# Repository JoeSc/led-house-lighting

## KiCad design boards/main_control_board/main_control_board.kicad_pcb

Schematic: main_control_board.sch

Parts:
C1, C101, C104, C107, C112, C116, C123, C148, C1001, C1234, C1235: CAP_0P1UF_10P_50V_X7R_0805; Voltage 50V
C2, C102, C109, C110, C126, C127: CAP_1UF_10P_25V_X7R_0805; Voltage 25V
C103, C117, C118, C119, C120, C121, C122, C128, C129, C130, C131, C142, C145, C1002, C1008, C1011: CAP_2P2UF_10P_50V_X5R_1206; Voltage 50V
C111, C113, C114, C12345: CAP_22UF_20P_10V_X5R_1206; Voltage 10V
C124, C125: CAP_39PF_5P_50V_NP0_0805; Voltage 50V
C132, C133, C134, C135, C136, C137, C138, C139, C140, C141: CAP_1UF_10P_50V_X5R_0805; Voltage 50V
D1, D2, D101, D103, D107, D108, D109: DIODE_MBR0520_SOD123
D4: LED_BLUE_0805
D102, D104: LED_GREEN_DIFF_0805
D105, D106: LED_YELLOW_0805
D110, D111, D112, D113, D114: DIODE_MBRA340T3G_SMA
HW100, HW101, HW102, HW103: CONN_1
J101, J102: CONN_USB_MINI_B
L101, L102, L103, L104, L105: IND_39UH
P1: CONN_JST_PH_4
P2, P101: CONN_JST_PH_3
P102: CONN_JST_PH_2
P103: CONN_2
P104: CONN_5X2
P105, P106: CONN_TERM_BLOCK_2POS_3P5MM
P107: CONN_TERM_BLOCK_4POS_3P5MM
Q101: TR_N_SI2308BDS
Q102: MOSFET_P
R1, R2: RES_1K_1P_1V8W_0805
R5, R101, R105, R108, R109: RES_330_1P_1V8W_0805
R102, R106, R107, R110: RES_4P7K_1P_1V8W_0805
R103: RES_1P5K_1P_1V8W_0805
R104: RES_100K_1P_1V8W_0805
R111, R112, R113, R114, R115: RES_4P42K_1P_1V8W_0805
R116, R117, R118, R119, R120: RES_80P6K_1P_1V8W_0805
SW101, SW102: SW_PB_MJTP1230
U101, U102, U103, U104, U105: IC_LM3414_PSOP8
U1000: IC_LPC1343_LQFP48
U1010: IC_FT232RL_SSOP28
U1020: IC_XBEE_SMD
U1050: IC_MCP1700T33_SOT23
X101: CRYSTAL_12MHZ_18PF_CS3P2X5

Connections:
+3.3V: C1.1, C101.1, C107.1, C109.1, C110.1, C111.1, C112.1, C113.1, C114.1, C123.1, C127.1, C1234.1, C1235.1, P1.1, P2.1, P101.2, P104.3, Q102.S, R1.1, R2.1, R5.2, R102.1, R107.1, R108.2, R109.2, R110.1, U1000.8, U1000.44, U1010.4, U1020.1, U1050.2
+5V: C102.1, C104.1, C126.1, C12345.1, D103.2, J101.1, P102.2 (PM), U1010.20, U1050.3
+24V: C103.1, C116.1, C117.1, C118.1, C119.1, C120.1, C121.1, C122.1, C128.1, C129.1, C130.1, C131.1, C137.1, C138.1, C139.1, C140.1, C141.1, C142.1, C145.1, C148.1, C1002.1, C1008.1, C1011.1, D110.2, D111.2, D112.2, D113.2, D114.2, P103.2 (PM), P105.2 (PM), P106.2 (PM), P107.4, U101.8, U102.8, U103.8, U104.8, U105.8
/AD1: P104.10, U1000.32
/AD2: P104.9, U1000.33
/AD3: P104.8, U1000.34
/AD4: P104.7, U1000.35
/BLU_DIM: U103.6, U1000.29
/BLU_FS: R118.1, U103.5
/BLU_IADJ: R113.1, U103.3
/BLU_OUT: C139.2, L103.1, P107.1
/BLU_SW: D112.1, L103.2, U103.7
/BLU_VCC: C134.1, U103.1
/BOOTSEL_RESET: D108.2, D109.2, SW102.2
/BOOT_SEL: C123.2, D1.1, D2.1, D108.1, R110.2, U1000.4
/EXTRA_AD: P2.2, U1000.42
/GRN_DIM: U102.6, U1000.30
/GRN_FS: R117.1, U102.5
/GRN_IADJ: R112.1, U102.3
/GRN_OUT: C138.2, L102.1, P107.2 (PM)
/GRN_SW: D111.1, L102.2, U102.7
/GRN_VCC: C133.1, U102.1
/IIC_SCL: P1.2, R2.2, U1000.15
/IIC_SDA: P1.3, R1.2, U1000.16
/MOTION_DET: P101.3, U1000.24
/RED_DIM: U101.6, U1000.40
/RED_FS: R116.1, U101.5
/RED_IADJ: R111.1, U101.3
/RED_OUT: C137.2, L101.1, P107.3
/RED_SW: D110.1, L101.2, U101.7
/RED_VCC: C132.1, U101.1
/RELAY_EN: Q101.G, U1000.45
/SER_RX_LED: D106.2, U1010.22
/SER_RX_LED_R: D106.1, R109.1
/SER_TX_LED: D105.2, U1010.23
/SER_TX_LED_R: D105.1, R108.1
/SER_UCTOUSB: U1000.47, U1010.5, U1020.3
/SER_USBTOUC: U1000.46, U1010.1, U1020.2
/SER_USB_D: J101.3, U1010.15
/SW1: P104.4, U1000.38
/SW2: P104.6, U1000.36
/SW3: P104.5, U1000.37
/SW4: P104.2, U1000.39
/UC_D: J102.3, R103.1, U1000.20
/UC_D_PU: Q102.D, R103.2, R105.1
/UC_USB_CONNECT: Q102.G, R107.2, U1000.22
/UC_VBUS: C2.1, D103.1, J102.1, R104.1, U1000.14
/UC_XI: C125.1, U1000.6, X101.1
/UC_XO: C124.1, U1000.7, X101.2
/USBTOUC_BOOT_SEL: D2.2, U1010.3
/WW2_DIM: U105.6, U1000.28
/WW2_FS: R120.1, U105.5
/WW2_IADJ: R115.1, U105.3
/WW2_OUT: C141.2, L105.1, P106.1
/WW2_SW: D114.1, L105.2, U105.7
/WW2_VCC: C136.1, U105.1
/WW_DIM: U104.6, U1000.27
/WW_FS: R119.1, U104.5
/WW_IADJ: R114.1, U104.3
/WW_OUT: C140.2, L104.1, P105.1
/WW_SW: D113.1, L104.2, U104.7
/WW_VCC: C135.1, U104.1
/XB_BOOT_SEL: D1.2, U1020.16
/XB_RSSI: D102.1, U1020.6
/~SER_RST: R106.1, U1010.19
/~SER_USB_D: J101.2, U1010.16
/~UC_D: J102.2, U1000.19
/~UC_RESET: D101.1, D107.1, D109.1, R102.2, SW101.2, U1000.3
/~USBTOUC_RESET: D107.2, U1010.2
/~XBEETOUC_RESET: D101.2, U1020.9
GND: C1.2, C2.2, C101.2, C102.2, C103.2, C104.2, C107.2, C109.2, C110.2, C111.2, C112.2, C113.2, C114.2, C116.2, C117.2, C118.2, C119.2, C120.2, C121.2, C122.2, C124.2, C125.2, C126.2, C127.2, C128.2, C129.2, C130.2, C131.2, C132.2, C133.2, C134.2, C135.2, C136.2, C142.2, C145.2, C148.2, C1001.2, C1002.2, C1008.2, C1011.2, C1234.2, C1235.2, C12345.2, D104.2, J101.5, J101.6, J102.5, J102.6, P1.4, P2.3, P101.1, P103.1, P104.1, Q101.S, R101.2, R104.2, R106.2, R111.2, R112.2, R113.2, R114.2, R115.2, R116.2, R117.2, R118.2, R119.2, R120.2, SW101.1, SW102.1, U101.2, U101.4, U102.2, U102.4, U103.2, U103.4, U104.2, U104.4, U105.2, U105.4, U1000.5, U1000.41, U1010.7, U1010.18, U1010.21, U1010.25, U1010.26, U1020.10, U1050.1
unnamed: C1001.1, U1010.17
unnamed: P102.1, Q101.D
unnamed: D104.1, R105.2
unnamed: D4.1, R5.1
unnamed: D102.2, R101.1
unnamed: D4.2, U1000.25

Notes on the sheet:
Mounting Holes
Add Series R on UC_VBUS to prevent accidental 5V short through UC
SW102 = Reset+Bootloader SW101= Reset

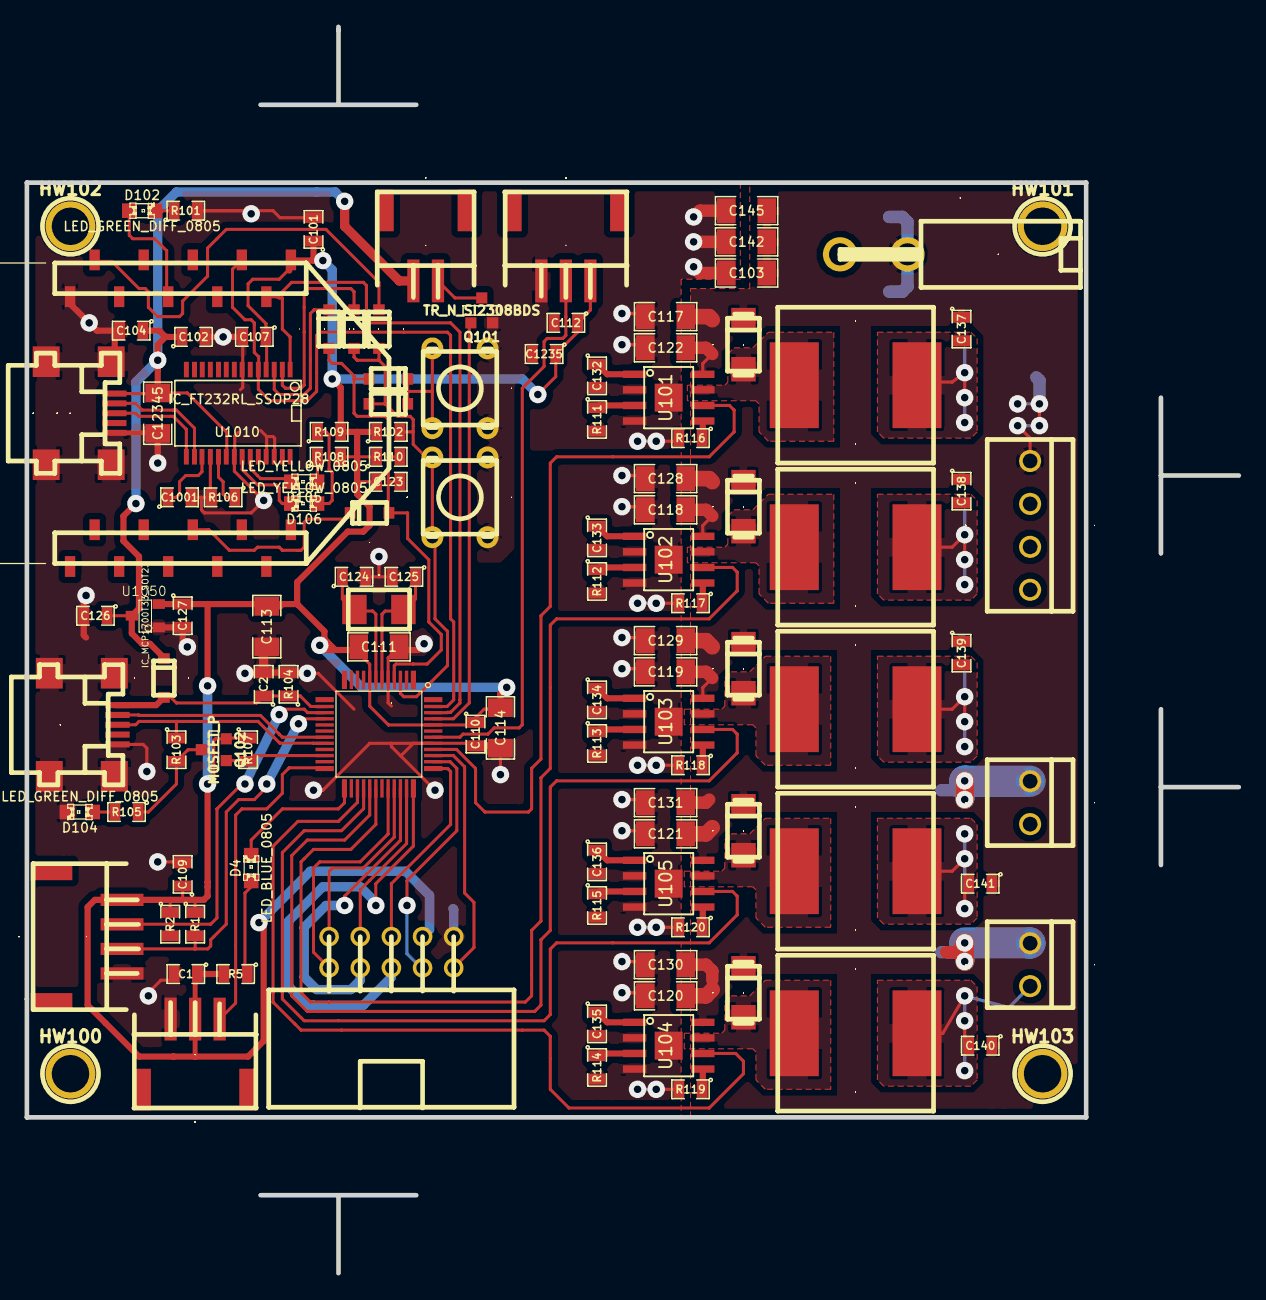
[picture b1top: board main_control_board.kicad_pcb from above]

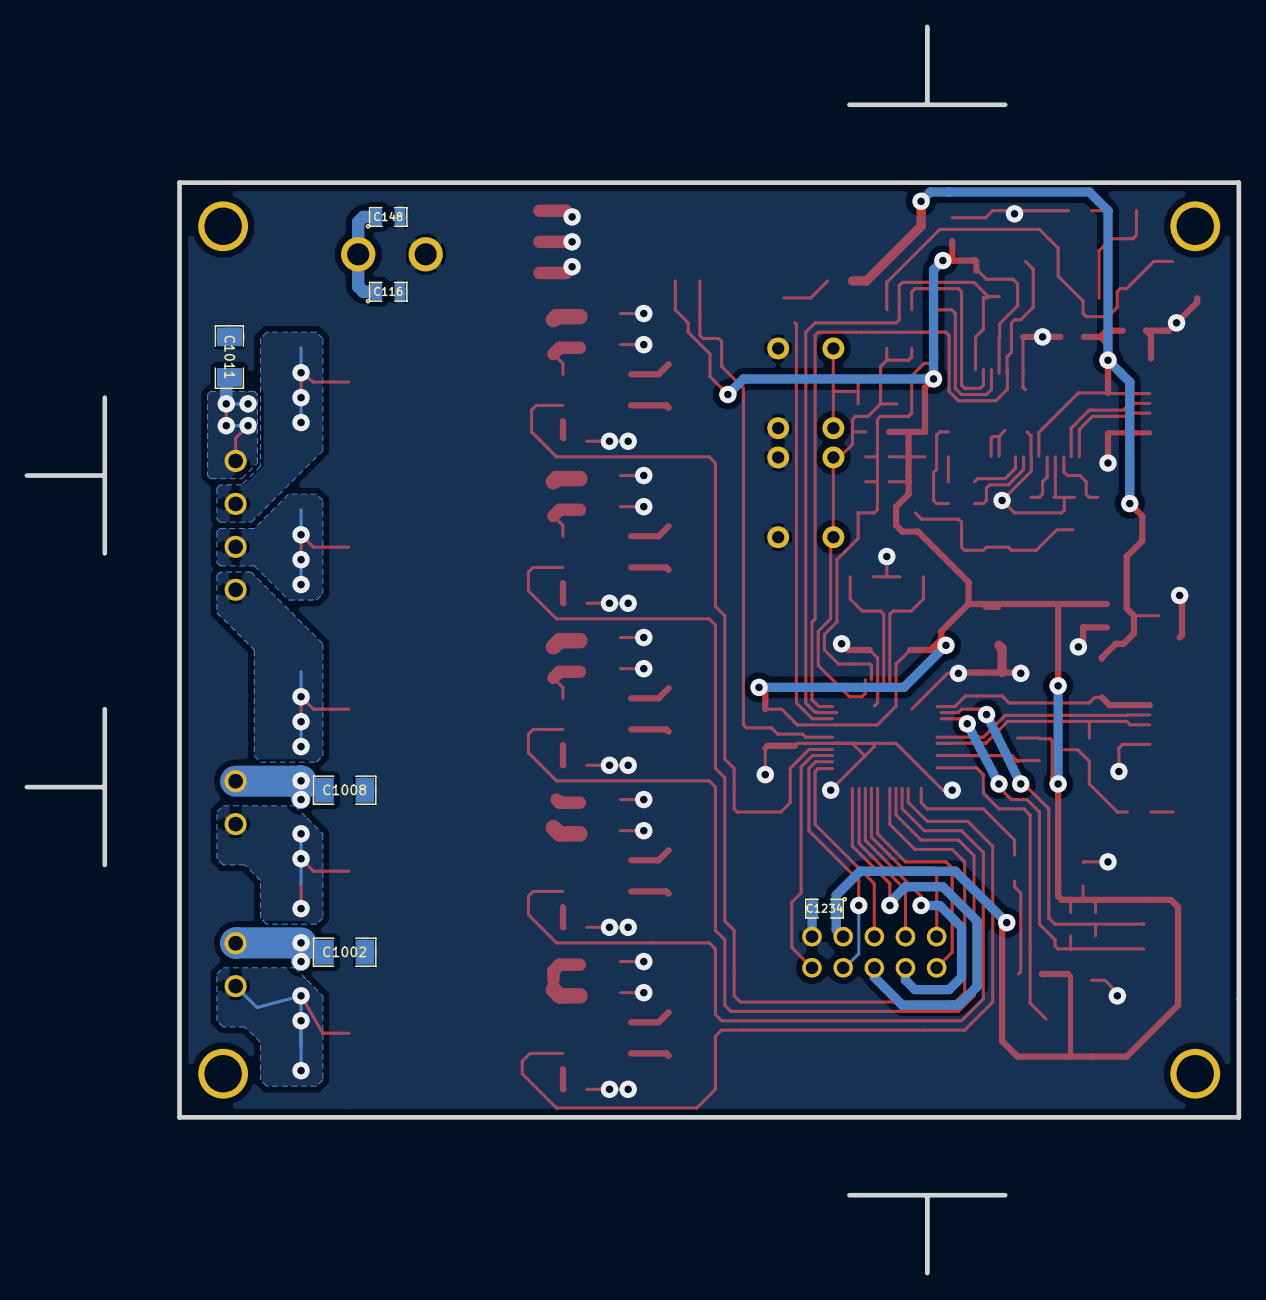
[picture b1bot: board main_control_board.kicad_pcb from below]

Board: 2 copper layers, 86.4 x 76.2 mm, 123 parts (6 on the bottom side), 77 nets.

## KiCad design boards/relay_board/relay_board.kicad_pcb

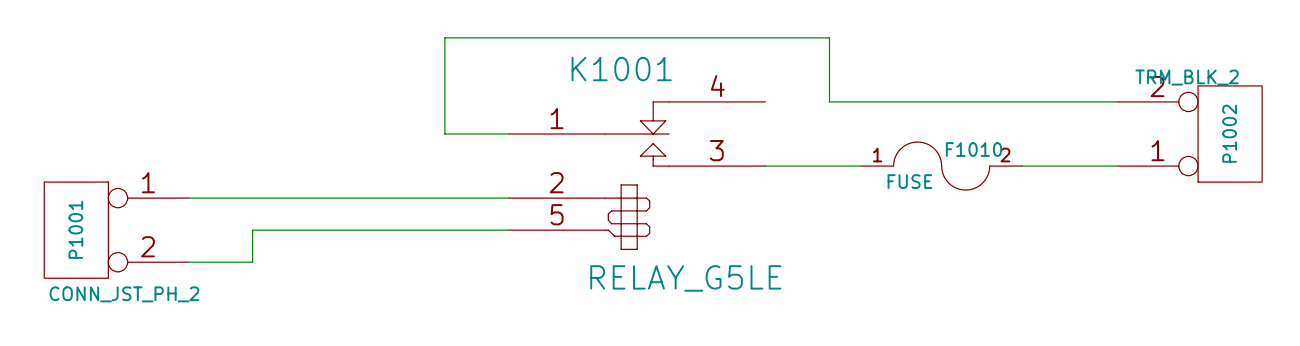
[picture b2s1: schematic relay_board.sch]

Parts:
F1010: FUSE
K1001: RELAY_G5LE
P1001: CONN_JST_PH_2
P1002: CONN_TERM_BLOCK_2POS_3P5MM

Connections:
unnamed: F1010.2, P1002.1
unnamed: F1010.1, K1001.3 (T1)
unnamed: K1001.5, P1001.2 (PM)
unnamed: K1001.2, P1001.1
unnamed: K1001.1 (C1), P1002.2 (PM)

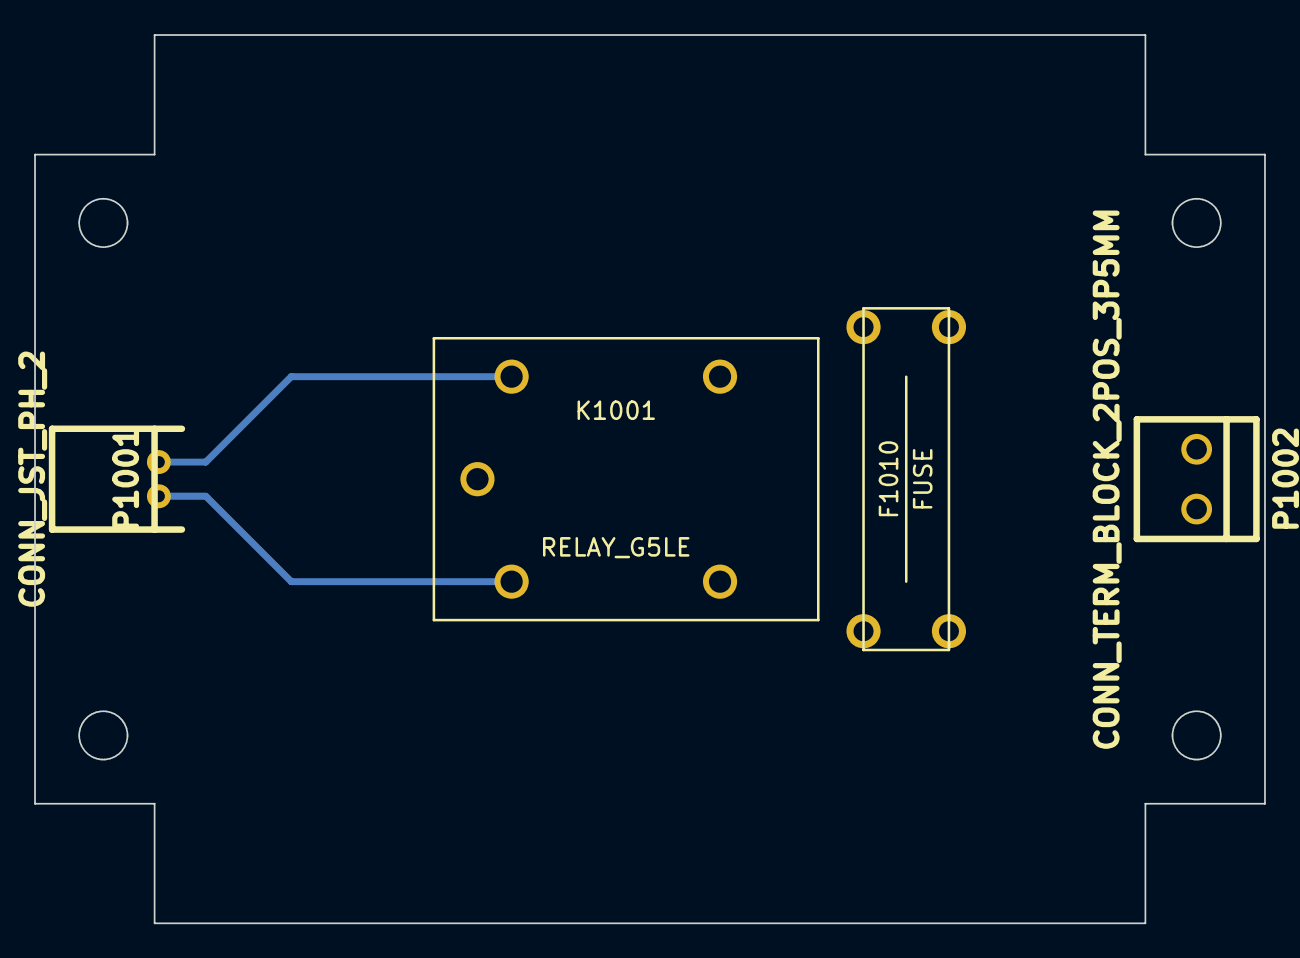
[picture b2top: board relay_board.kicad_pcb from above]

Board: 2 copper layers, 72.0 x 52.0 mm, 4 parts (0 on the bottom side), 5 nets.

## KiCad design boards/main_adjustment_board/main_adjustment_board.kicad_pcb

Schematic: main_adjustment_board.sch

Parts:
C101: CAP_22UF_20P_10V_X5R_1206; Voltage 10V
C102, C103, C104, C105: CAP_0P1UF_10P_50V_X7R_0805; Voltage 50V
D101: LED
P101: CONN_5X2
P102, P103, P104, P105: CONN_1
R101, R102: RES_0_0P_1V4_1206
R103: R
RV101, RV102, RV103, RV104: POT_10K_SLIDER
SW101, SW102, SW103: SW_PB_MJTP1230

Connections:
+3.3V: C101.1, C102.1, C103.1, C104.1, C105.1, R101.1, RV101.1, RV102.1, RV103.1, RV104.1
/AD1: P101.2
/AD2: P101.1
/AD3: P101.4
/AD4: P101.3
/SW1: P101.7, SW103.2
/SW2: D101.1 (A), P101.6
/SW3: P101.5, SW102.2
/SW4: P101.9, SW101.2
GND: C101.2, C102.2, C103.2, C104.2, C105.2, R102.2, R103.2, RV101.3, RV102.3, RV103.3, RV104.3, SW101.1, SW102.1, SW103.1
unnamed: P101.8, R101.2
unnamed: D101.2 (K), R103.1
unnamed: P101.10, R102.1

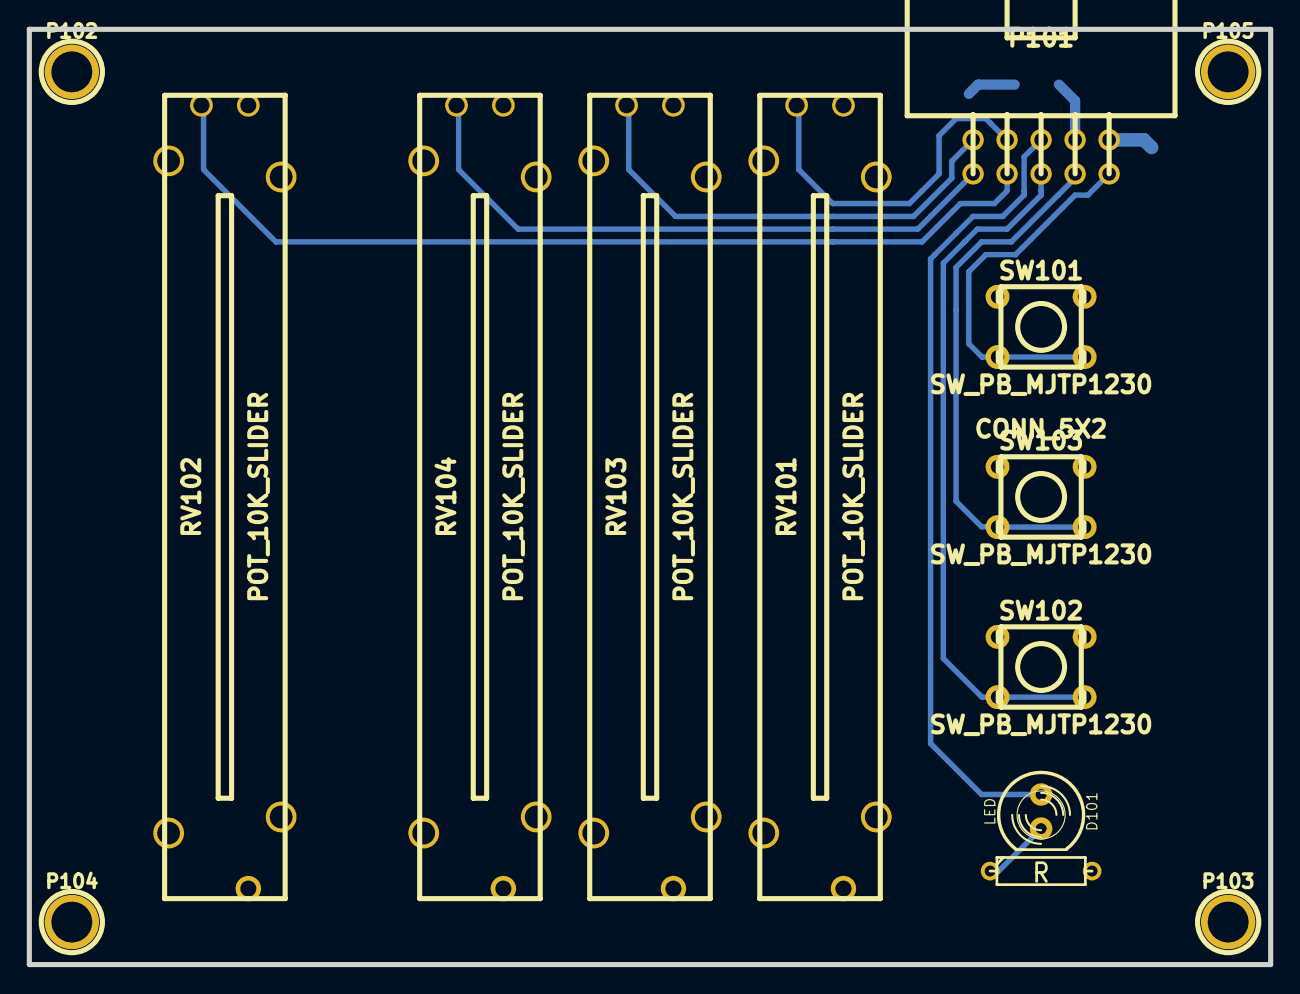
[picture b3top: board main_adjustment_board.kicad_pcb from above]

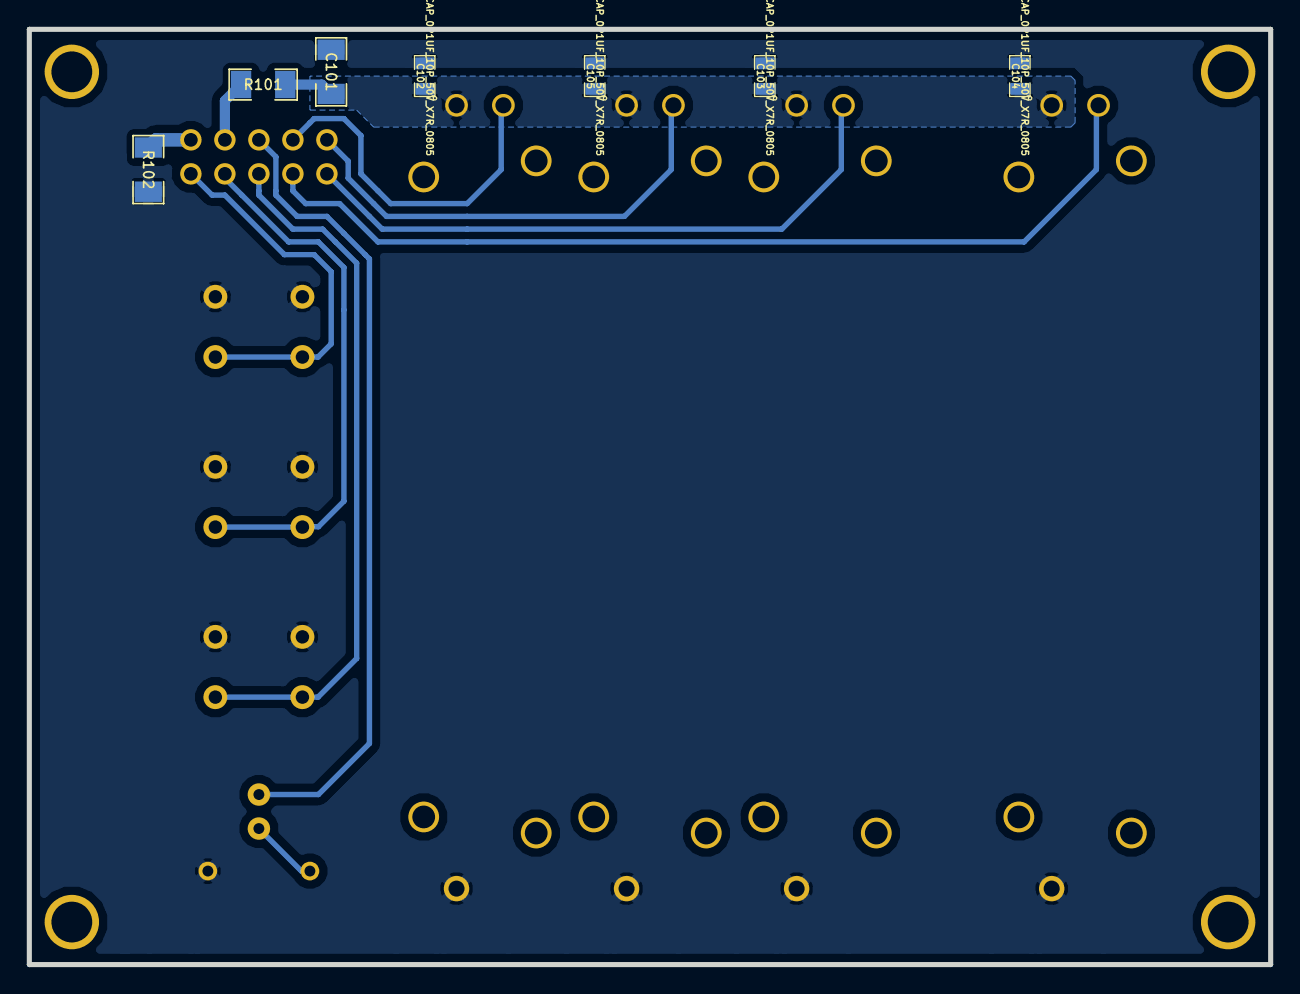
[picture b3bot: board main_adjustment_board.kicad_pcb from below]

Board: 2 copper layers, 92.7 x 69.8 mm, 21 parts (7 on the bottom side), 9 nets.

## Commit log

2013-03-23 software/main_control_board
    Added main control board software with basic functionality
2013-06-11 Added Boards
2013-08-29 Modifications
2013-08-29 Added above_cabinet_breakout
2013-08-29 Added under_cab_breakout
2013-08-29 main_control_board
    Fixed the adjustment board ribbon cable connector pinout
